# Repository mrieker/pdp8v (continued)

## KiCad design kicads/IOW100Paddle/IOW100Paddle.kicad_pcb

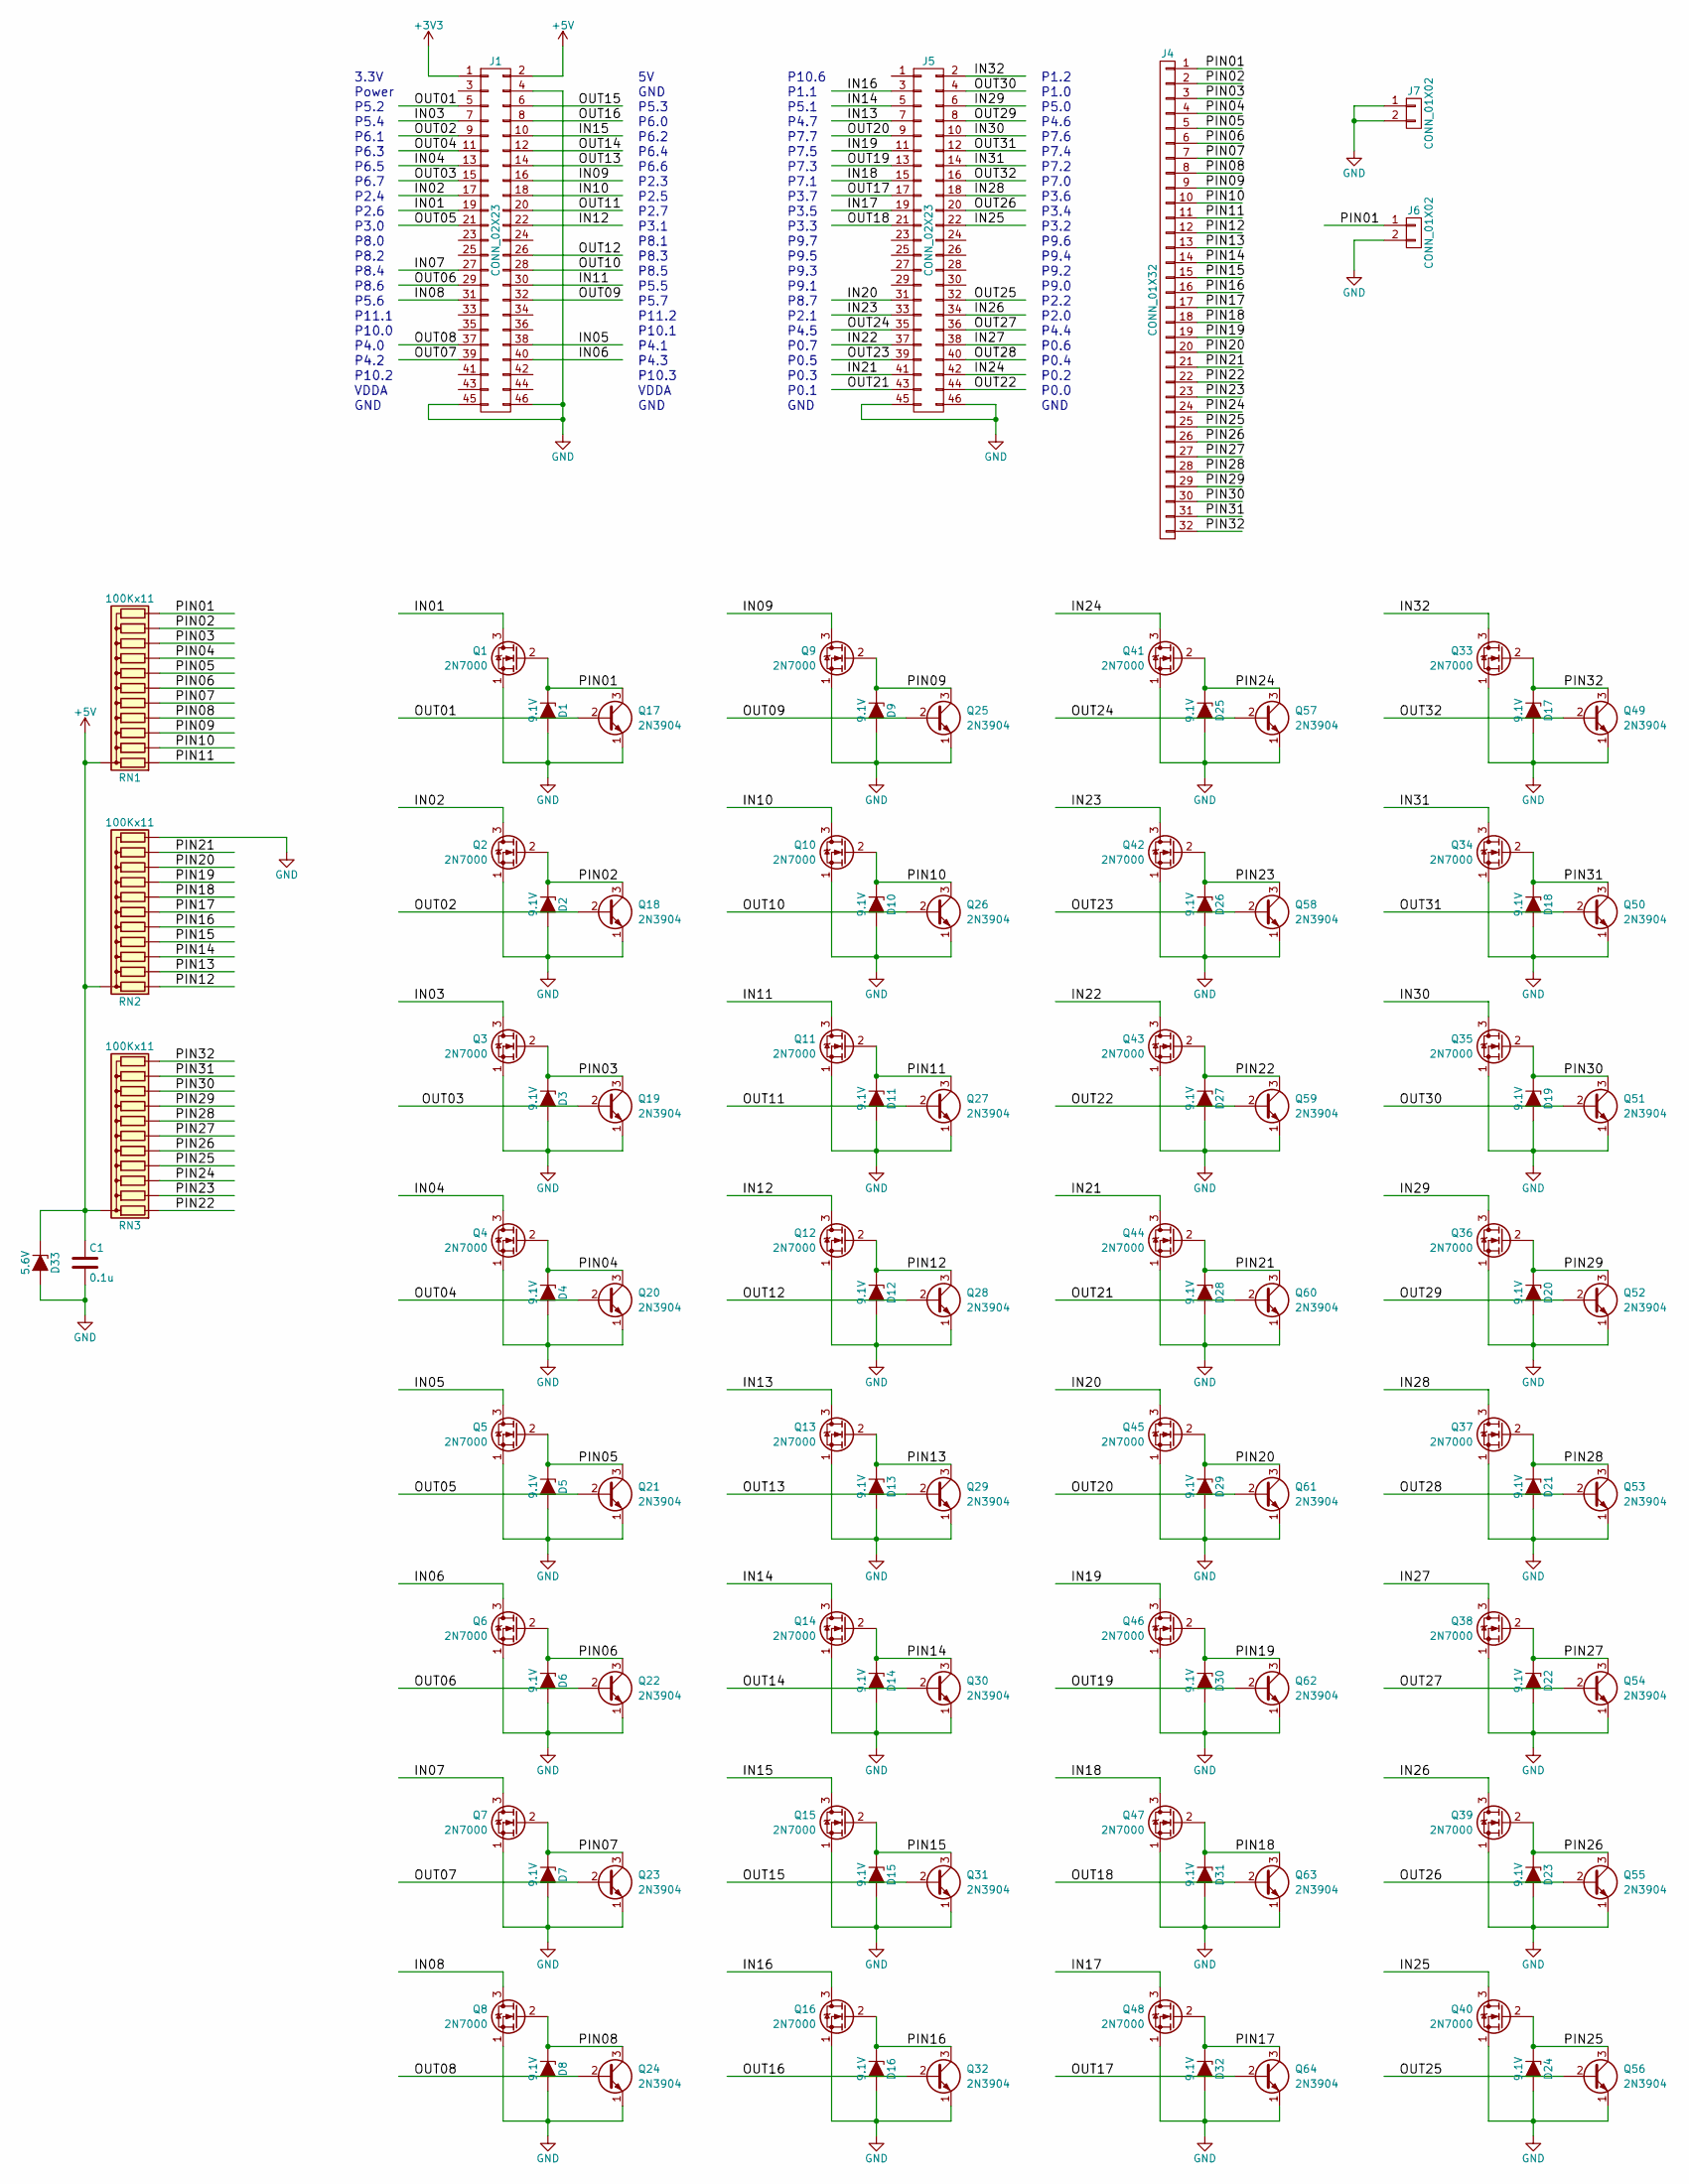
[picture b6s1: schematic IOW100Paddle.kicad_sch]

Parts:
C1: 0.1u; C_Axial_L3.8mm_D2.6mm_P7.50mm_Horizontal
D1, D2, D3, D4, D5, D6, D7, D8, D9, D10, D11, D12, D13, D14, D15, D16, D17, D18, D19, D20, D21, D22, D23, D24, D25, D26, D27, D28, D29, D30, D31, D32: 9.1V; D_DO-35_SOD27_P6.35mm_Horizontal
D33: 5.6V; D_DO-35_SOD27_P6.35mm_Horizontal
J1, J5: CONN_02X23; Pin_Header_Straight_2x23_Pitch2.54mm
J4: CONN_01X32; Pin_Header_Straight_1x32_Pitch2.54mm
J6, J7: CONN_01X02; Pin_Header_Straight_1x02_Pitch2.54mm
Q1, Q2, Q3, Q4, Q5, Q6, Q7, Q8, Q9, Q10, Q11, Q12, Q13, Q14, Q15, Q16, Q33, Q34, Q35, Q36, Q37, Q38, Q39, Q40, Q41, Q42, Q43, Q44, Q45, Q46, Q47, Q48: 2N7000; TO-92_Molded_Wide
Q17, Q18, Q19, Q20, Q21, Q22, Q23, Q24, Q25, Q26, Q27, Q28, Q29, Q30, Q31, Q32, Q49, Q50, Q51, Q52, Q53, Q54, Q55, Q56, Q57, Q58, Q59, Q60, Q61, Q62, Q63, Q64: 2N3904; TO-92_Molded_Wide
RN1, RN2, RN3: 100Kx11; R_Array_SIP12

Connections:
+3V3: J1.1
+5V: C1.1, D33.1 (K), J1.2, RN1.1 (common), RN2.1 (common), RN3.1 (common)
/IN01: J1.19, Q1.3 (D)
/IN02: J1.17, Q2.3 (D)
/IN03: J1.7, Q3.3 (D)
/IN04: J1.13, Q4.3 (D)
/IN05: J1.38, Q5.3 (D)
/IN06: J1.40, Q6.3 (D)
/IN07: J1.27, Q7.3 (D)
/IN08: J1.31, Q8.3 (D)
/IN09: J1.16, Q9.3 (D)
/IN10: J1.18, Q10.3 (D)
/IN11: J1.30, Q11.3 (D)
/IN12: J1.22, Q12.3 (D)
/IN13: J5.7, Q13.3 (D)
/IN14: J5.5, Q14.3 (D)
/IN15: J1.10, Q15.3 (D)
/IN16: J5.3, Q16.3 (D)
/IN17: J5.19, Q48.3 (D)
/IN18: J5.15, Q47.3 (D)
/IN19: J5.11, Q46.3 (D)
/IN20: J5.31, Q45.3 (D)
/IN21: J5.41, Q44.3 (D)
/IN22: J5.37, Q43.3 (D)
/IN23: J5.33, Q42.3 (D)
/IN24: J5.42, Q41.3 (D)
/IN25: J5.22, Q40.3 (D)
/IN26: J5.34, Q39.3 (D)
/IN27: J5.38, Q38.3 (D)
/IN28: J5.18, Q37.3 (D)
/IN29: J5.6, Q36.3 (D)
/IN30: J5.10, Q35.3 (D)
/IN31: J5.14, Q34.3 (D)
/IN32: J5.2, Q33.3 (D)
/OUT01: J1.5, Q17.2 (B)
/OUT02: J1.9, Q18.2 (B)
/OUT03: J1.15, Q19.2 (B)
/OUT04: J1.11, Q20.2 (B)
/OUT05: J1.21, Q21.2 (B)
/OUT06: J1.29, Q22.2 (B)
/OUT07: J1.39, Q23.2 (B)
/OUT08: J1.37, Q24.2 (B)
/OUT09: J1.32, Q25.2 (B)
/OUT10: J1.28, Q26.2 (B)
/OUT11: J1.20, Q27.2 (B)
/OUT12: J1.26, Q28.2 (B)
/OUT13: J1.14, Q29.2 (B)
/OUT14: J1.12, Q30.2 (B)
/OUT15: J1.6, Q31.2 (B)
/OUT16: J1.8, Q32.2 (B)
/OUT17: J5.17, Q64.2 (B)
/OUT18: J5.21, Q63.2 (B)
/OUT19: J5.13, Q62.2 (B)
/OUT20: J5.9, Q61.2 (B)
/OUT21: J5.43, Q60.2 (B)
/OUT22: J5.44, Q59.2 (B)
/OUT23: J5.39, Q58.2 (B)
/OUT24: J5.35, Q57.2 (B)
/OUT25: J5.32, Q56.2 (B)
/OUT26: J5.20, Q55.2 (B)
/OUT27: J5.36, Q54.2 (B)
/OUT28: J5.40, Q53.2 (B)
/OUT29: J5.8, Q52.2 (B)
/OUT30: J5.4, Q51.2 (B)
/OUT31: J5.12, Q50.2 (B)
/OUT32: J5.16, Q49.2 (B)
/PIN01: D1.1 (K), J4.1, J6.1, Q1.2 (G), Q17.3 (C), RN1.12 (R11)
/PIN02: D2.1 (K), J4.2, Q2.2 (G), Q18.3 (C), RN1.11 (R10)
/PIN03: D3.1 (K), J4.3, Q3.2 (G), Q19.3 (C), RN1.10 (R9)
/PIN04: D4.1 (K), J4.4, Q4.2 (G), Q20.3 (C), RN1.9 (R8)
/PIN05: D5.1 (K), J4.5, Q5.2 (G), Q21.3 (C), RN1.8 (R7)
/PIN06: D6.1 (K), J4.6, Q6.2 (G), Q22.3 (C), RN1.7 (R6)
/PIN07: D7.1 (K), J4.7, Q7.2 (G), Q23.3 (C), RN1.6 (R5)
/PIN08: D8.1 (K), J4.8, Q8.2 (G), Q24.3 (C), RN1.5 (R4)
/PIN09: D9.1 (K), J4.9, Q9.2 (G), Q25.3 (C), RN1.4 (R3)
/PIN10: D10.1 (K), J4.10, Q10.2 (G), Q26.3 (C), RN1.3 (R2)
/PIN11: D11.1 (K), J4.11, Q11.2 (G), Q27.3 (C), RN1.2 (R1)
/PIN12: D12.1 (K), J4.12, Q12.2 (G), Q28.3 (C), RN2.2 (R1)
/PIN13: D13.1 (K), J4.13, Q13.2 (G), Q29.3 (C), RN2.3 (R2)
/PIN14: D14.1 (K), J4.14, Q14.2 (G), Q30.3 (C), RN2.4 (R3)
/PIN15: D15.1 (K), J4.15, Q15.2 (G), Q31.3 (C), RN2.5 (R4)
/PIN16: D16.1 (K), J4.16, Q16.2 (G), Q32.3 (C), RN2.6 (R5)
/PIN17: D32.1 (K), J4.17, Q48.2 (G), Q64.3 (C), RN2.7 (R6)
/PIN18: D31.1 (K), J4.18, Q47.2 (G), Q63.3 (C), RN2.8 (R7)
/PIN19: D30.1 (K), J4.19, Q46.2 (G), Q62.3 (C), RN2.9 (R8)
/PIN20: D29.1 (K), J4.20, Q45.2 (G), Q61.3 (C), RN2.10 (R9)
/PIN21: D28.1 (K), J4.21, Q44.2 (G), Q60.3 (C), RN2.11 (R10)
/PIN22: D27.1 (K), J4.22, Q43.2 (G), Q59.3 (C), RN3.2 (R1)
/PIN23: D26.1 (K), J4.23, Q42.2 (G), Q58.3 (C), RN3.3 (R2)
/PIN24: D25.1 (K), J4.24, Q41.2 (G), Q57.3 (C), RN3.4 (R3)
/PIN25: D24.1 (K), J4.25, Q40.2 (G), Q56.3 (C), RN3.5 (R4)
/PIN26: D23.1 (K), J4.26, Q39.2 (G), Q55.3 (C), RN3.6 (R5)
/PIN27: D22.1 (K), J4.27, Q38.2 (G), Q54.3 (C), RN3.7 (R6)
/PIN28: D21.1 (K), J4.28, Q37.2 (G), Q53.3 (C), RN3.8 (R7)
/PIN29: D20.1 (K), J4.29, Q36.2 (G), Q52.3 (C), RN3.9 (R8)
/PIN30: D19.1 (K), J4.30, Q35.2 (G), Q51.3 (C), RN3.10 (R9)
/PIN31: D18.1 (K), J4.31, Q34.2 (G), Q50.3 (C), RN3.11 (R10)
/PIN32: D17.1 (K), J4.32, Q33.2 (G), Q49.3 (C), RN3.12 (R11)
GND: C1.2, D1.2 (A), D2.2 (A), D3.2 (A), D4.2 (A), D5.2 (A), D6.2 (A), D7.2 (A), D8.2 (A), D9.2 (A), D10.2 (A), D11.2 (A), D12.2 (A), D13.2 (A), D14.2 (A), D15.2 (A), D16.2 (A), D17.2 (A), D18.2 (A), D19.2 (A), D20.2 (A), D21.2 (A), D22.2 (A), D23.2 (A), D24.2 (A), D25.2 (A), D26.2 (A), D27.2 (A), D28.2 (A), D29.2 (A), D30.2 (A), D31.2 (A), D32.2 (A), D33.2 (A), J1.4, J1.45, J1.46, J5.45, J5.46, J6.2, J7.1, J7.2, Q1.1 (S), Q2.1 (S), Q3.1 (S), Q4.1 (S), Q5.1 (S), Q6.1 (S), Q7.1 (S), Q8.1 (S), Q9.1 (S), Q10.1 (S), Q11.1 (S), Q12.1 (S), Q13.1 (S), Q14.1 (S), Q15.1 (S), Q16.1 (S), Q17.1 (E), Q18.1 (E), Q19.1 (E), Q20.1 (E), Q21.1 (E), Q22.1 (E), Q23.1 (E), Q24.1 (E), Q25.1 (E), Q26.1 (E), Q27.1 (E), Q28.1 (E), Q29.1 (E), Q30.1 (E), Q31.1 (E), Q32.1 (E), Q33.1 (S), Q34.1 (S), Q35.1 (S), Q36.1 (S), Q37.1 (S), Q38.1 (S), Q39.1 (S), Q40.1 (S), Q41.1 (S), Q42.1 (S), Q43.1 (S), Q44.1 (S), Q45.1 (S), Q46.1 (S), Q47.1 (S), Q48.1 (S), Q49.1 (E), Q50.1 (E), Q51.1 (E), Q52.1 (E), Q53.1 (E), Q54.1 (E), Q55.1 (E), Q56.1 (E), Q57.1 (E), Q58.1 (E), Q59.1 (E), Q60.1 (E), Q61.1 (E), Q62.1 (E), Q63.1 (E), Q64.1 (E), RN2.12 (R11)

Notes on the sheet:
VDDA
P6.0
P3.3
P10.6
P8.0
P4.3
P2.1
P5.5
P7.4
P0.4
P6.4
P1.1
P9.5
P5.7
P2.3
P5.6
P4.6
P3.1
P0.7
P5.1
GND
P6.7
P8.7
P3.7
P6.6
P6.2
P0.5
Power
P7.5
P7.2
3.3V
P8.6
P3.2
P2.2
P11.2
P0.1
P2.0
P8.1
P4.7
P5.2

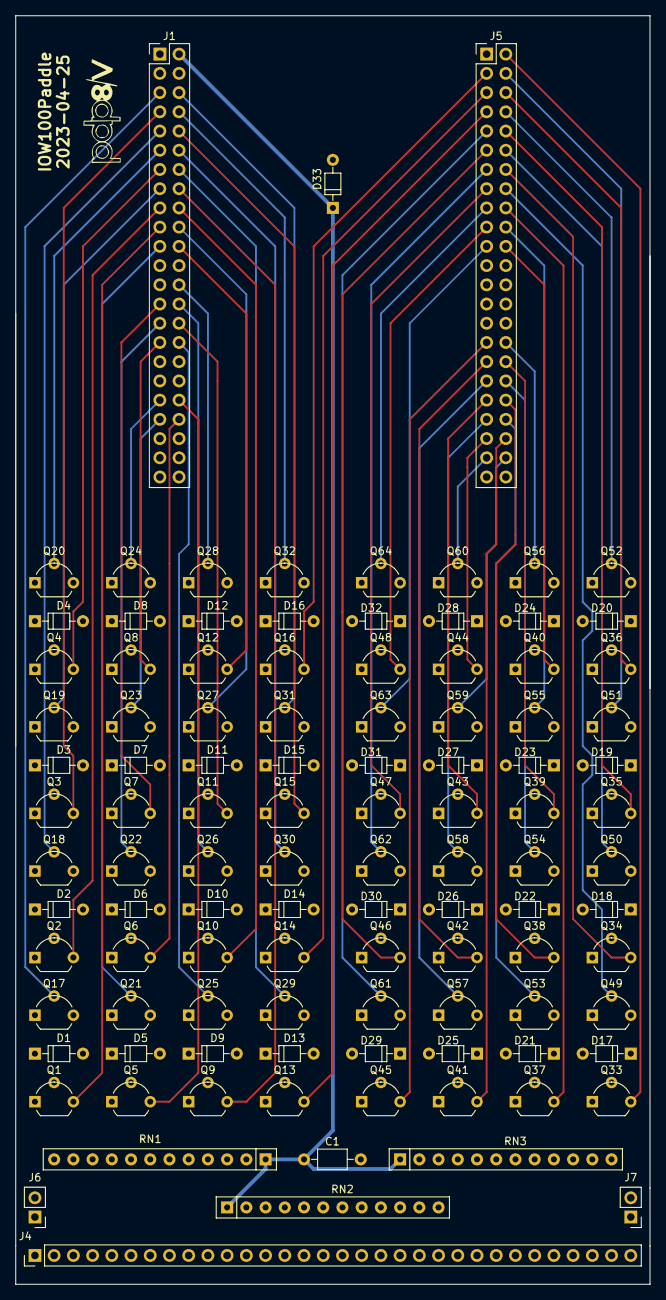
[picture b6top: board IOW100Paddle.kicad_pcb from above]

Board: 4 copper layers, 83.8 x 167.6 mm, 106 parts (0 on the bottom side), 98 nets.

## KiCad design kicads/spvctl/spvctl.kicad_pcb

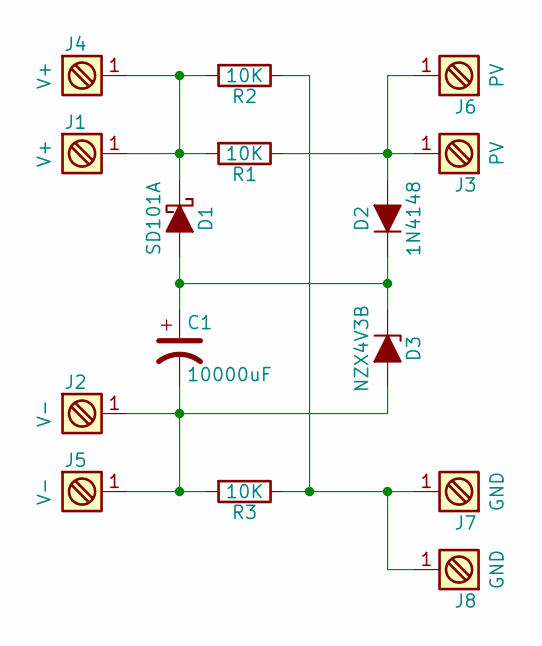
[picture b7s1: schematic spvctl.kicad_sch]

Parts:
C1: 10000uF; CP_Radial_D16.0mm_P7.50mm
D1: SD101A; D_DO-35_SOD27_P7.62mm_Horizontal
D2: 1N4148; D_DO-35_SOD27_P7.62mm_Horizontal
D3: NZX4V3B; D_DO-35_SOD27_P7.62mm_Horizontal
J1, J4: V+; PINTST
J2, J5: V-; PINTST
J3, J6: PV; PINTST
J7, J8: GND; PINTST
R1, R2, R3: 10K; R_Axial_DIN0207_L6.3mm_D2.5mm_P7.62mm_Horizontal

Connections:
unnamed: C1.1, D1.2 (A), D2.1 (K), D3.1 (K)
unnamed: C1.2, D3.2 (A), J2.1, J5.1, R3.2
unnamed: D1.1 (K), J1.1, J4.1, R1.2, R2.2
unnamed: D2.2 (A), J3.1, J6.1, R1.1
unnamed: J7.1, J8.1, R2.1, R3.1

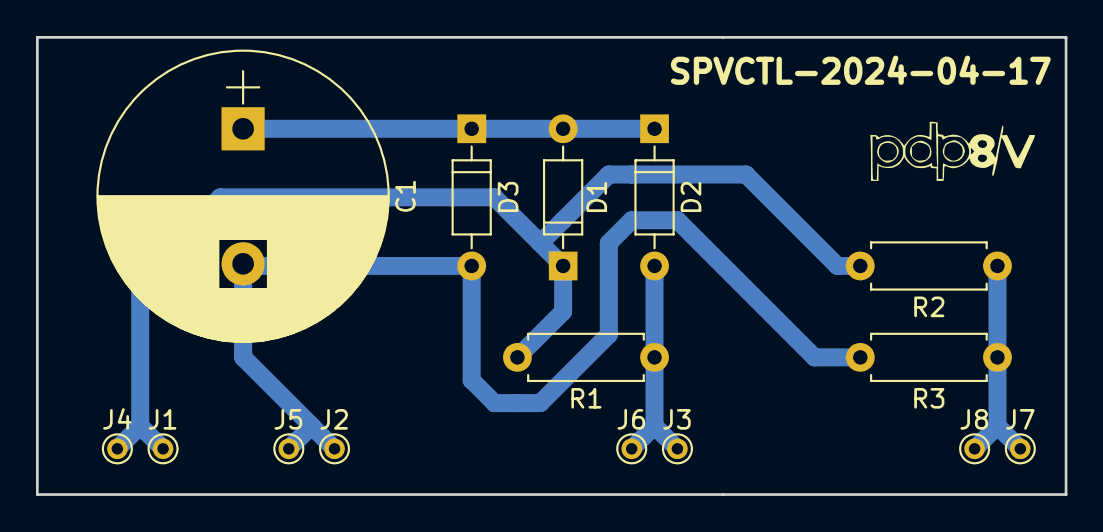
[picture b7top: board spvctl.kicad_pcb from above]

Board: 2 copper layers, 57.1 x 25.4 mm, 15 parts (0 on the bottom side), 5 nets.

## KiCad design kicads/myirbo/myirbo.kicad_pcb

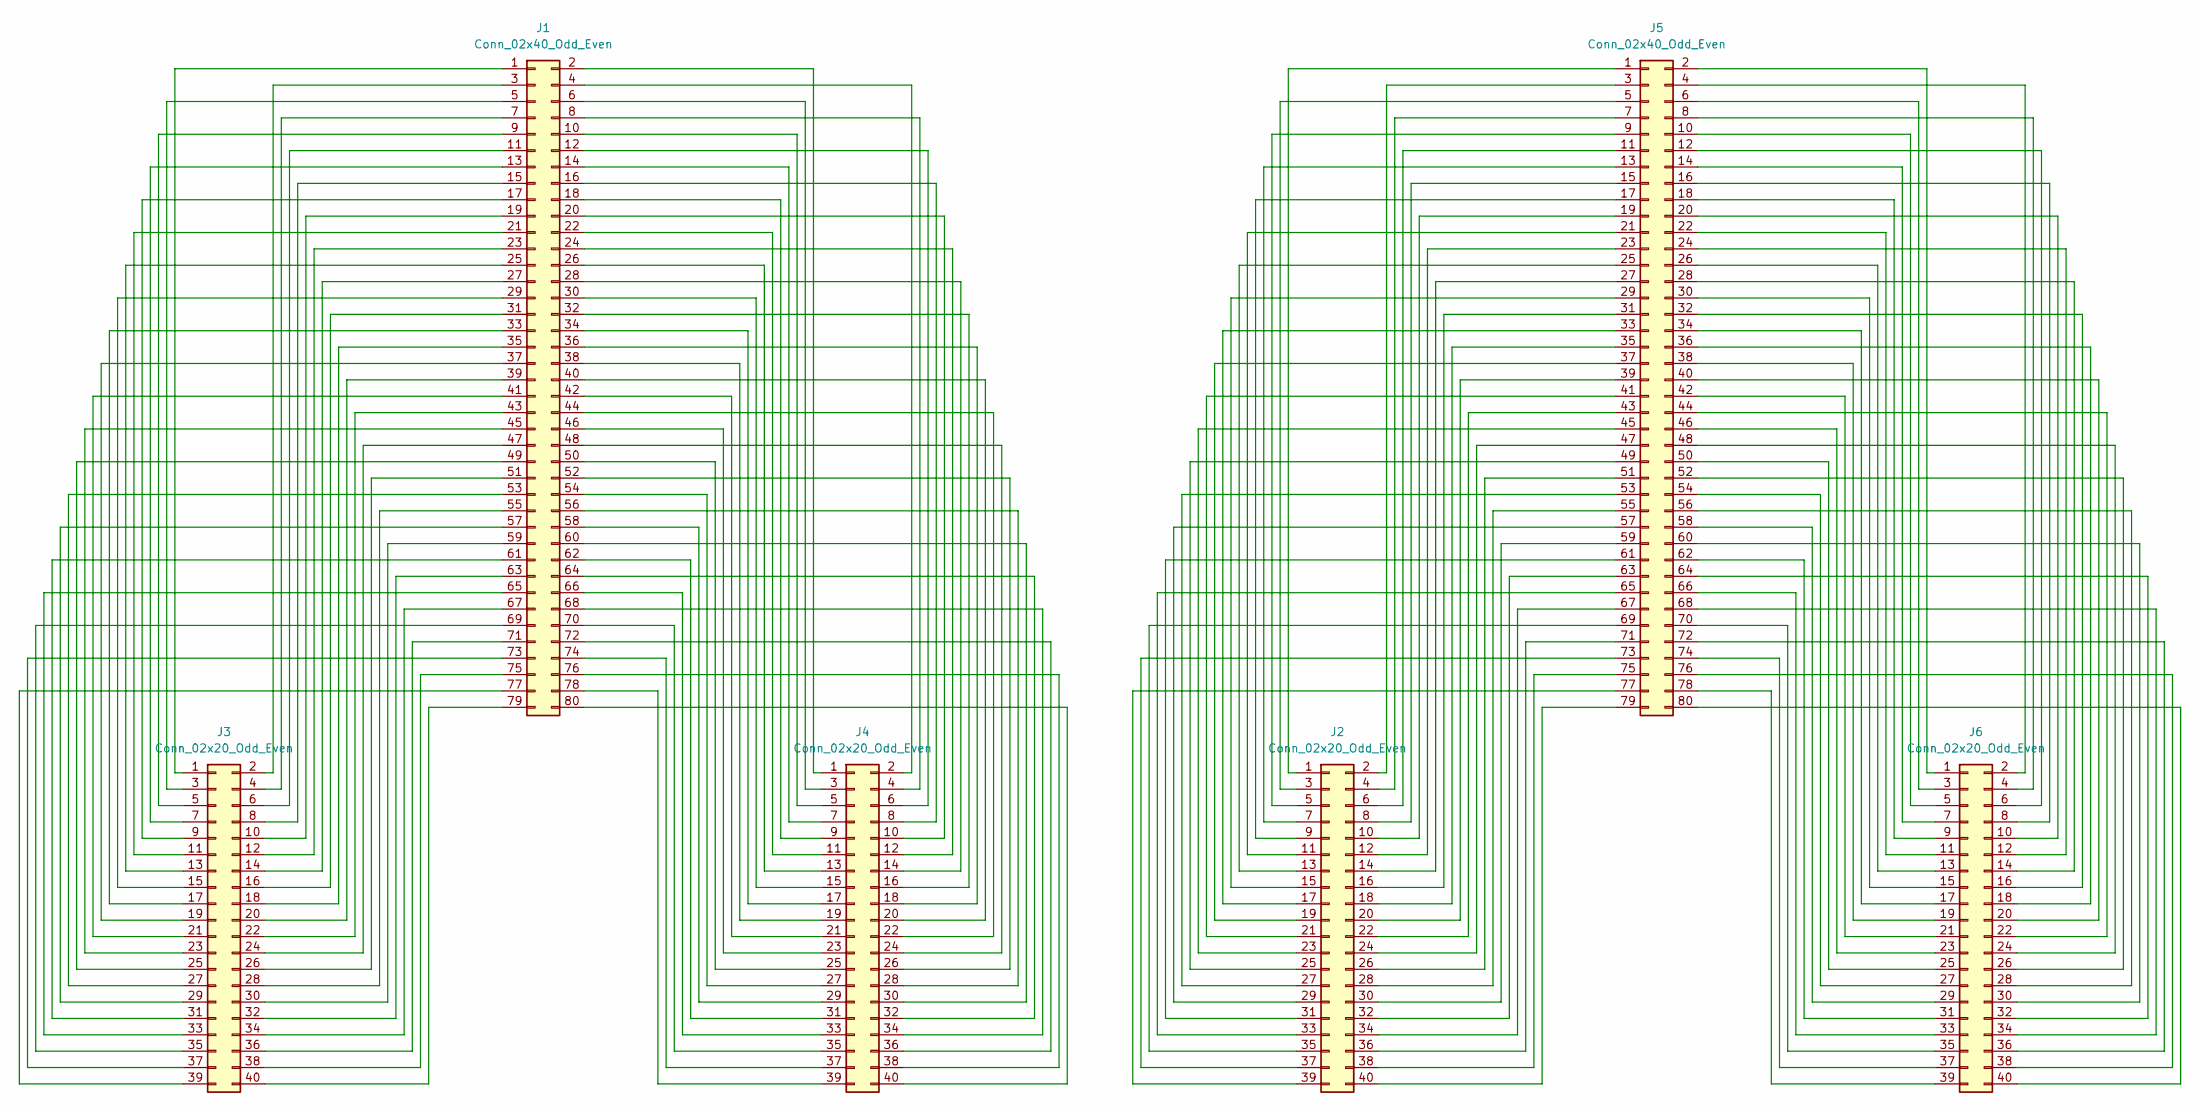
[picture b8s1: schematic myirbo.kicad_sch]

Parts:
J1, J5: Conn_02x40_Odd_Even; PinHeader_2x40_P1.27mm_Vertical
J2, J3, J4, J6: Conn_02x20_Odd_Even; PinHeader_2x20_P2.54mm_Vertical

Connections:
unnamed: J1.1, J3.1
unnamed: J1.2, J4.1
unnamed: J1.3, J3.2
unnamed: J1.4, J4.2
unnamed: J1.5, J3.3
unnamed: J1.6, J4.3
unnamed: J1.7, J3.4
unnamed: J1.8, J4.4
unnamed: J1.9, J3.5
unnamed: J1.10, J4.5
unnamed: J1.11, J3.6
unnamed: J1.12, J4.6
unnamed: J1.13, J3.7
unnamed: J1.14, J4.7
unnamed: J1.15, J3.8
unnamed: J1.16, J4.8
unnamed: J1.17, J3.9
unnamed: J1.18, J4.9
unnamed: J1.19, J3.10
unnamed: J1.20, J4.10
unnamed: J1.21, J3.11
unnamed: J1.22, J4.11
unnamed: J1.23, J3.12
unnamed: J1.24, J4.12
unnamed: J1.25, J3.13
unnamed: J1.26, J4.13
unnamed: J1.27, J3.14
unnamed: J1.28, J4.14
unnamed: J1.29, J3.15
unnamed: J1.30, J4.15
unnamed: J1.31, J3.16
unnamed: J1.32, J4.16
unnamed: J1.33, J3.17
unnamed: J1.34, J4.17
unnamed: J1.35, J3.18
unnamed: J1.36, J4.18
unnamed: J1.37, J3.19
unnamed: J1.38, J4.19
unnamed: J1.39, J3.20
unnamed: J1.40, J4.20
unnamed: J1.41, J3.21
unnamed: J1.42, J4.21
unnamed: J1.43, J3.22
unnamed: J1.44, J4.22
unnamed: J1.45, J3.23
unnamed: J1.46, J4.23
unnamed: J1.47, J3.24
unnamed: J1.48, J4.24
unnamed: J1.49, J3.25
unnamed: J1.50, J4.25
unnamed: J1.51, J3.26
unnamed: J1.52, J4.26
unnamed: J1.53, J3.27
unnamed: J1.54, J4.27
unnamed: J1.55, J3.28
unnamed: J1.56, J4.28
unnamed: J1.57, J3.29
unnamed: J1.58, J4.29
unnamed: J1.59, J3.30
unnamed: J1.60, J4.30
unnamed: J1.61, J3.31
unnamed: J1.62, J4.31
unnamed: J1.63, J3.32
unnamed: J1.64, J4.32
unnamed: J1.65, J3.33
unnamed: J1.66, J4.33
unnamed: J1.67, J3.34
unnamed: J1.68, J4.34
unnamed: J1.69, J3.35
unnamed: J1.70, J4.35
unnamed: J1.71, J3.36
unnamed: J1.72, J4.36
unnamed: J1.73, J3.37
unnamed: J1.74, J4.37
unnamed: J1.75, J3.38
unnamed: J1.76, J4.38
unnamed: J1.77, J3.39
unnamed: J1.78, J4.39
unnamed: J1.79, J3.40
unnamed: J1.80, J4.40
unnamed: J2.1, J5.1
unnamed: J2.2, J5.3
unnamed: J2.3, J5.5
unnamed: J2.4, J5.7
unnamed: J2.5, J5.9
unnamed: J2.6, J5.11
unnamed: J2.7, J5.13
unnamed: J2.8, J5.15
unnamed: J2.9, J5.17
unnamed: J2.10, J5.19
unnamed: J2.11, J5.21
unnamed: J2.12, J5.23
unnamed: J2.13, J5.25
unnamed: J2.14, J5.27
unnamed: J2.15, J5.29
unnamed: J2.16, J5.31
unnamed: J2.17, J5.33
unnamed: J2.18, J5.35
unnamed: J2.19, J5.37
unnamed: J2.20, J5.39
unnamed: J2.21, J5.41
unnamed: J2.22, J5.43
unnamed: J2.23, J5.45
unnamed: J2.24, J5.47
unnamed: J2.25, J5.49
unnamed: J2.26, J5.51
unnamed: J2.27, J5.53
unnamed: J2.28, J5.55
unnamed: J2.29, J5.57
unnamed: J2.30, J5.59
unnamed: J2.31, J5.61
unnamed: J2.32, J5.63
unnamed: J2.33, J5.65
unnamed: J2.34, J5.67
unnamed: J2.35, J5.69
unnamed: J2.36, J5.71
unnamed: J2.37, J5.73
unnamed: J2.38, J5.75
unnamed: J2.39, J5.77
unnamed: J2.40, J5.79
unnamed: J5.2, J6.1
unnamed: J5.4, J6.2
unnamed: J5.6, J6.3
unnamed: J5.8, J6.4
unnamed: J5.10, J6.5
unnamed: J5.12, J6.6
unnamed: J5.14, J6.7
unnamed: J5.16, J6.8
unnamed: J5.18, J6.9
unnamed: J5.20, J6.10
unnamed: J5.22, J6.11
unnamed: J5.24, J6.12
unnamed: J5.26, J6.13
unnamed: J5.28, J6.14
unnamed: J5.30, J6.15
unnamed: J5.32, J6.16
unnamed: J5.34, J6.17
unnamed: J5.36, J6.18
unnamed: J5.38, J6.19
unnamed: J5.40, J6.20
unnamed: J5.42, J6.21
unnamed: J5.44, J6.22
unnamed: J5.46, J6.23
unnamed: J5.48, J6.24
unnamed: J5.50, J6.25
unnamed: J5.52, J6.26
unnamed: J5.54, J6.27
unnamed: J5.56, J6.28
unnamed: J5.58, J6.29
unnamed: J5.60, J6.30
unnamed: J5.62, J6.31
unnamed: J5.64, J6.32
unnamed: J5.66, J6.33
unnamed: J5.68, J6.34
unnamed: J5.70, J6.35
unnamed: J5.72, J6.36
unnamed: J5.74, J6.37
unnamed: J5.76, J6.38
unnamed: J5.78, J6.39
unnamed: J5.80, J6.40

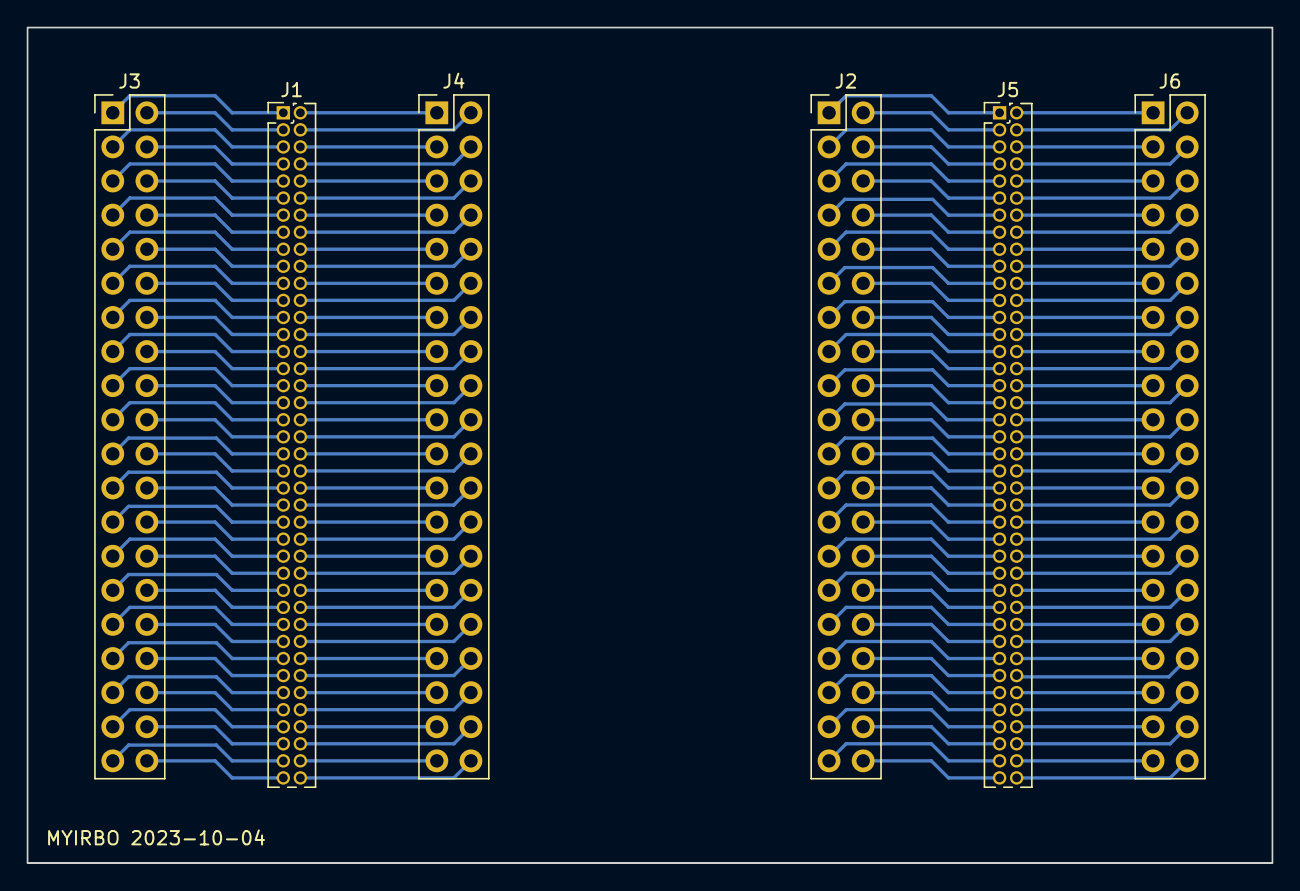
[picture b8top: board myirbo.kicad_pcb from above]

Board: 2 copper layers, 92.7 x 62.2 mm, 6 parts (0 on the bottom side), 160 nets.

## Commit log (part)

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2024-02-29 initial release
2024-03-04 couple small fixes
    * fix compiler warnings for unchecked syscall return values
    * change default clocking speed so it clocks around 25 kcps average
    * fix driver makefile to build whole.mod and NetGen if needed for -csrclib stuff
    * add -rimloader to raspictl so it can load rim format files
    ./raspictl -rimloader -startpc -0200 CONWAY.RIM
    * add -resetonerr to raspictl so it will reset & restart on error
2024-03-13 add RESET and LD IF/PC buttons to GUI screen
    also refactor backplane out in zynq so it could be used with de0
    ...but my de0 board is dead
2024-03-19 various changes
    - add gpl headers to source files
    - add scripting to raspictl so can dynamically load papertape and disk files
    also can access various other state
    - allow multiple teletypes (for edusystem basic 20)
    - use telnet to access teletypes
2024-04-02 mostly added dectape plus other changes
    add sizes and trace utilities
    print number of triodes on in raspictl -mintimes
    print number/rates of instructions in raspictl -mintimes
    implement emulated dectape
    - driver/raspictl iodevtty
    - maindec/tc08 d3bc
2024-04-08 mostly added dynamic disassembly
    - raspictl tcl script command dyndis
    disassembles based on executing instructions
    other changes:
    raspictl dectape: gofast parameter to eliminate delays
    tty: split debug levels for all io instructions and characters
    memext: ioreset shouldn't reset dframe,iframe (some maindec failed)
2024-04-26 add latest generated pcb links to README.md
2024-04-26 use README.txt instead of .md
2024-05-27 driver: have iodevrk8je create file if non-existant
2024-05-27 scheme: update scheme.asm set! to just overwrite SE_VALU entry
    --- does not work
2024-05-27 kicads: add missing bwlogo.png file
2024-05-27 driver: add tclboardtest.cc
2024-05-27 netgen: add dff's abcd gate locations to report file
2024-05-27 driver: add syncsh command to tclboardtest
2024-05-27 driver: add shadowing to tclboardtest
2024-05-27 driver: add alu equation to tcltestini dump alu,seq commands
    also add reset and step commands
2024-05-27 driver: add dumping more boards to tclboardtest
    ...and fix up exam of G_LINK,G_DATA pins
2024-05-27 update .gitignore to ignore .so files
2024-05-27 driver: add tcltestini.tcl to tclboardtest
2024-05-31 driver: add walking LED to autoboardtest rpi
2024-05-31 zynqlib: fix segfault on exit
2024-06-02 driver: add resetting to -tubesaver processing
    ...to 'save' the reset circuitry by toggling it
    reset simply sets PC to 0 and state to FETCH1
2024-06-06 kicads: get updated schematics for KiCad 7.0
    IOW100Paddle, eight, spvctl
2024-06-06 driver: add -csrclib option to autoboardtest
2024-06-06 zynq: clean up zynq code some
    and add missing AddNTO.java file
2024-06-14 zynq: have paddles act wire-anded with bus like real paddles
2024-06-14 driver: fix -tubesaver reset cycle in raspictl
2024-06-14 driver: print initial register contents on startup
2024-06-14 scheme: update test.sh file for new iodevtty
2024-06-14 driver: add paddles to nohwlib
    and move readgpio function from shadow to nohwlib
2024-06-23 modules: consolidate consbody.inc into cons.inc
2024-06-23 zynq: fix gating irq onto bus from seq board
2024-06-23 driver: add -exitonerror and -runtime options to autoboardtest
    ...and have abtevery.sh stop on any error
2024-06-23 modules: fix some comments
2024-06-25 edu20c: add working edusystem-20 basic
2024-06-29 driver: add -quick option to iodev ptape load command
    ...to speed up edu20c loading
2024-06-29 driver: fix up paper tape reader/punch so it works with edu20c basic
    - fix interrupt request
    - add -ascii option when loading files
2024-06-29 add howto-runstuff.txt file
2024-06-30 driver: fix up focal69 startup script
    and consolidate tubesaver option into scriptini.tcl
2024-07-04 driver: minor code cleanup in nohwlib.cc
2024-07-04 silly: have doubleroll sense SR
    count number of steps in SR then flip direction
2024-07-04 driver: fix up instruction step to stop at INTAK1 as well as FETCH2
    also fix up gui LDADDR/EXAM/DEP/RUN/HALT buttons
2024-07-04 scheme: clean up some scheme startup scripts
2024-07-06 driver: fix nohwlib derivation of mq/mql when QENA=0
    ...should be 0s not 1s
    also fix segment fault on exit with -pidp enabled
    also fix display of stepcounter in pidp leds
2024-07-10 little code cleanup
2024-07-15 silly: flip SC light back and forth in doubleroll for pidp panel
2024-07-17 driver: gray out memory buttons on GUI when processor running
2024-07-17 driver: make reset consistent across interfaces
    make sure if,df get reset in all cases
    no default startpc
2024-07-22 os8: include OS/8 source disk
2024-07-22 driver: fix dectape support
    - fix debug prints gated by debug setting
    - support ioskipwait optimization
    - update wordcount before writing block number in search so os8 works
    - any error should clear go bit
2024-07-22 asm: add octtobin utility to convert link output files to binloader
2024-07-22 driver: fix up paper tape -ascii mode to work better with OS/8
    on punch:
    strip nulls
    strip CRs
    strip control-Z
    zero all bit <7>s
    on read:
2024-07-23 driver: get os/8 dectape to boot
    ...by outputting words very slowly when dma buffer overlaps PC
    also rename dtape stuff to tc08
2024-07-23 driver: rename dtapestatus to tc08status
2024-07-27 focal: update help to include ptape -ascii option
2024-07-27 driver: add VC8 video display device
2024-07-27 driver: support VC8/I and VC8/E style video displays
    sample programs:
    VC8/I : silly/drawbox.asm
    VC8/E : silly/kaleid.pal
2024-07-29 driver: support red/green colors for VC8/E
2024-07-29 driver: speed up -nohwlib simulator
    ABCD was taking a long time to zero the struct in constructor
2024-07-29 driver: vc8 print point draw rate once per minute if -mintimes option
2024-07-29 silly: use red/green colors in kalied.pal
2024-07-29 silly: cycle through shift counts automatically in kaleid
    ...and update MQ,SC leds in case of PiDP panel
2024-07-31 driver: add reference counts to dynamic disassembly (dyndis)
2024-07-31 silly: just use shift count 2,3 for kaleidoscope
    and other small optimizations, speeds it up 20%
    also include shell script to compile and start it
2024-07-31 silly: fix some comments in kalied.pal and .sh
2024-08-04 driver: use find command to locate tcl.h for makefile
2024-08-04 silly: have kalied stay in each shift count for 4096 points
    ...instead of 'random' so it stays drawing in each style for same time
2024-08-04 driver: VC8 support varying window size
    scale drawing to fit
2024-08-09 driver: defer creating TC08 shared memory until it is needed
2024-08-09 driver: add iodev tty halton & inject commands for writing test scripts
    halton halts processor when one of the given strings is seen on tty output
    inject injects characters into keyboard stream
2024-08-15 driver: fix tty inject to work even kb directed to /dev/null
2024-08-15 driver: lock rk05 and tc08 files that work over nfs
2024-08-20 driver: simplify zynqlib
2024-08-20 driver: make new csrcmod_proc a little more efficient
2024-08-20 driver: separate out stopping from halting
    stopping - commanded by gui or script
    halting - HLT instruction (or optimized IOSKIP/JMP.-1)
2024-08-22 driver: add -echo option to tty inject command
    waits for each character to be echoed before injecting next
2024-08-22 maindec: modernize maindec run scripts
    cd maindec
    ./run_<testname>.sh <option>
    option = none to run on tubes
    -csrclib : use gate-level PC simulator (medium)
    -nohwlib : use cycle-level PC simulator (fast)
    -zynqlib : use zynq fpga simulator at tube speed
2024-08-23 maindec: fix up tc08 test scripts
2024-08-25 silly: kaleid SR<11> on shows big circle, off is normal
2024-08-25 driver: avoid hanging on control-C or other terminating signal
    call exit() from a thread other than main() in case main() has
    a mutex locked and exithandler() locks a mutex that main() has
2024-08-25 driver: display changed VC8 screen size in upper left corner
    also check VC8 max screen size so it doesn't crash
2024-08-28 driver: clean up control-C with scripts
    set stopreason to CONTROL_C
    two control-Cs in a row force exit
2024-09-02 driver: blank out state leds when doing ldad/exam/dep on pidp panel
    and use lookup tables in pidp.cc to map leds & switches
2024-09-08 driver: make HLT always stop the processor
    ...not wait-for-interrupt
    added WFI instruction 06313
2024-09-24 driver: fix loadmod.sh if it needs to load 2 modules
    ...like for zynq
2024-09-24 driver: fix -randmem halting
2024-09-24 silly: have doubleroll mq leds switch direction with everything else
2024-09-24 driver: add assemop script command to assemble an instruction
2024-09-30 zynq: add missing zynq file myboard_wrapper.vhd
    also fix up makentov.sh script that creates <boardname>_nto.v files
    and update howto-build.txt
2024-09-30 driver,zynq: use frontpanel.v switchregister switches
    ...instead of envar switchregister or TCL script swreg
2024-09-30 driver,zynq: get i2c code working
    ...for testing pipanel
2024-09-30 zynq: swap frontpanel.v MCP23017 A<->B pins to match actual PCB
2024-09-30 driver: add debug prints to ZynqLib::fpstopped()
2024-10-01 zynq: attempt to get zynq's /dev/i2c-0 to talk to frontpanel
    ...gets occasional timeout errors
2024-11-30 add octtorim program to create rim format files
2024-12-01 scheme: conditionalize to run on pdp-8/l
2025-10-12 add back panel librecad drawing
    holds (4) filament power supplies
    (2) high-voltage power supplies
    (1) 5V power supply
    (5) 2-prong AC outlets for fans
    (2) 3-prong AC inlets for power cords
    (1) 3-prong AC outlet for test equipment
2025-10-13 add front panel librecad drawing
2025-11-29 fix backplane shorted VPP connector by ground pad
    protection diode cathode was shorted to ground
    also turn filament connectors 90 degrees for easier wiring
2025-11-29 update zynq build scripts to sort stuff like 1134 zynq
    also don't require i2c console for zynq
2025-11-30 I2C-based paddle board schematic and layout
2025-11-30 update README.txt
    add some build instructions
2025-12-01 add easynixie-based frequency counter
    arduino source and circuit board design
2025-12-13 add life game demo program
    adapted from LIFE.BA from OS/8:
    1 REM LIFE CLARK BAKER 3/72 C.O.G.
    2 REMARKABLY TRANSLATED TO OS8 BASIC BY KAY R. FISHER ...DEC
2025-12-20 have nixie frequency counter only display cycle frequency
    comment out alternating with instruction frequency
2025-12-20 fix some comments in seq.mod
2025-12-27 use WFI instruction to wait for interrupt in dttest.asm
2025-12-31 set up a timeout for reading from the iowarrior paddles
2025-12-31 consolidate clockup/clockdn calls in raspictl for easier debugging
2025-12-31 update kaleid.sh to include default switchregister setting
